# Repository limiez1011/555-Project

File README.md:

# blinky
Little led board that uses a 555 timer to clock a decade counter.

## Functionality
The NE555 is in AStable mode which creates a PWM signal that feeds into the CD4017, the PWM output is adjustable through the potentiometer, the CD4017 has 10 output pins which turn on sequentially every time it recieves a clock pulse, on our PCB this means that the leds will turn on after another in a circular pattern.

## BOM
- 1x NE555 Timer
- 1x CD4017 Decade counter
- 1x Potentiometer
- 2x Capacitors
- 2x Resistors
- 10x LED's

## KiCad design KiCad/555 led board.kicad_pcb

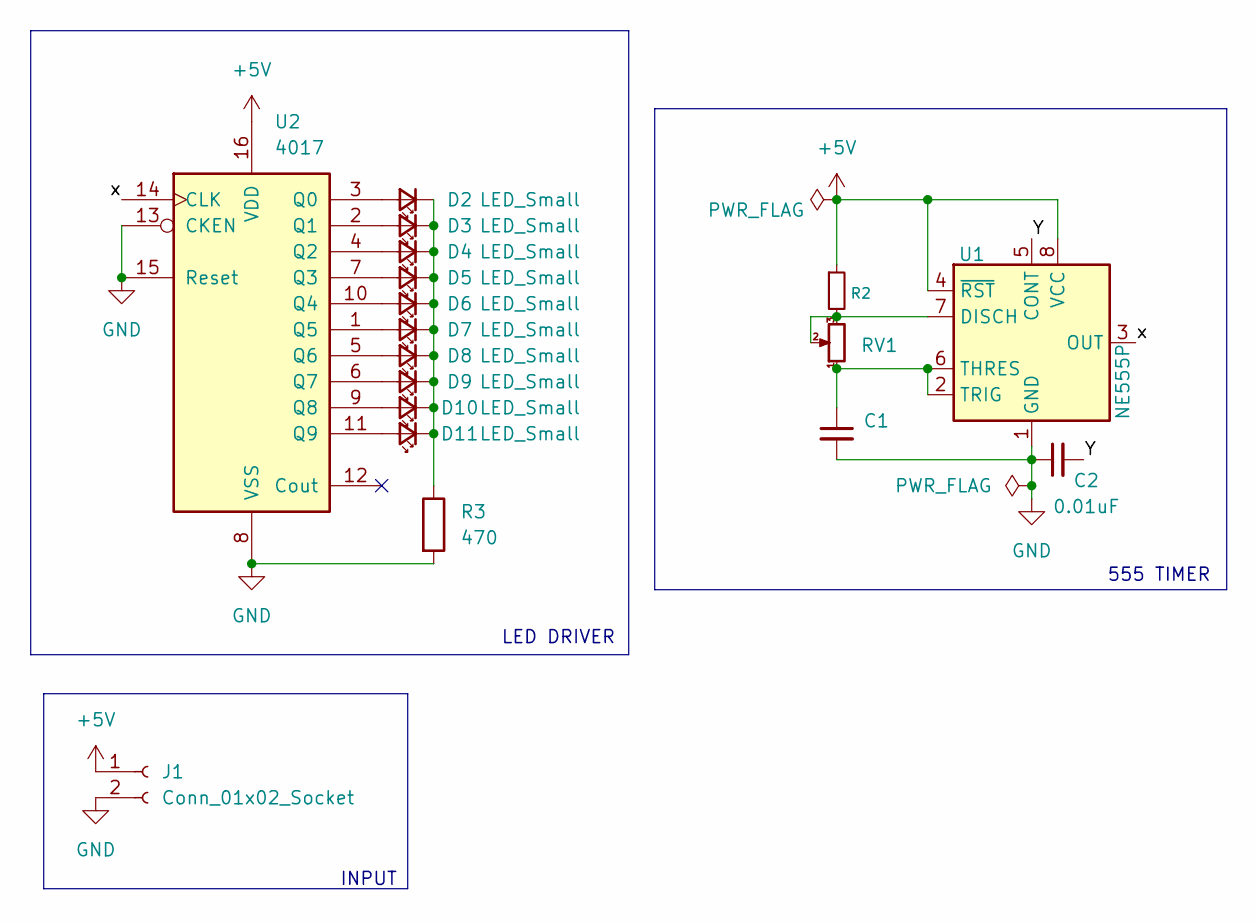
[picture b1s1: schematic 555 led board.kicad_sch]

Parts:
C1: C_Small; CP_Radial_D5.0mm_P2.00mm
C2: 0.01uF; C_Disc_D7.5mm_W2.5mm_P5.00mm
D2, D3, D4, D5, D6, D7, D8, D9, D10, D11: LED_Small; LED_D3.0mm
J1: Conn_01x02_Socket; PinHeader_1x02_P2.54mm_Vertical
R2: R_Small; R_Axial_DIN0207_L6.3mm_D2.5mm_P7.62mm_Horizontal
R3: 470; R_Axial_DIN0207_L6.3mm_D2.5mm_P7.62mm_Horizontal
RV1: R_Potentiometer_Small; Potentiometer_Vishay_T93YA_Vertical
U1: NE555P; DIP-8_W7.62mm
U2: 4017; DIP794W45P254L1969H508Q16

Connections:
+5V: J1.1, R2.1, U1.4 (~RST), U1.8 (VCC), U2.16 (VDD)
/Y: C2.2, U1.5 (CONT)
/x: U1.3 (OUT), U2.14 (CLK)
GND: C1.2, C2.1, J1.2, R3.2, U1.1 (GND), U2.8 (VSS), U2.13 (CKEN), U2.15 (Reset)
unnamed: D2.2 (A), U2.3 (Q0)
unnamed: D3.2 (A), U2.2 (Q1)
unnamed: D4.2 (A), U2.4 (Q2)
unnamed: D5.2 (A), U2.7 (Q3)
unnamed: D6.2 (A), U2.10 (Q4)
unnamed: D7.2 (A), U2.1 (Q5)
unnamed: D8.2 (A), U2.5 (Q6)
unnamed: D9.2 (A), U2.6 (Q7)
unnamed: D10.2 (A), U2.9 (Q8)
unnamed: D2.1 (K), D3.1 (K), D4.1 (K), D5.1 (K), D6.1 (K), D7.1 (K), D8.1 (K), D9.1 (K), D10.1 (K), D11.1 (K), R3.1
unnamed: D11.2 (A), U2.11 (Q9)
unnamed: R2.2, RV1.2, RV1.3, U1.7 (DISCH)
unnamed: C1.1, RV1.1, U1.2 (TRIG), U1.6 (THRES)

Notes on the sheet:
INPUT
LED DRIVER
555 TIMER

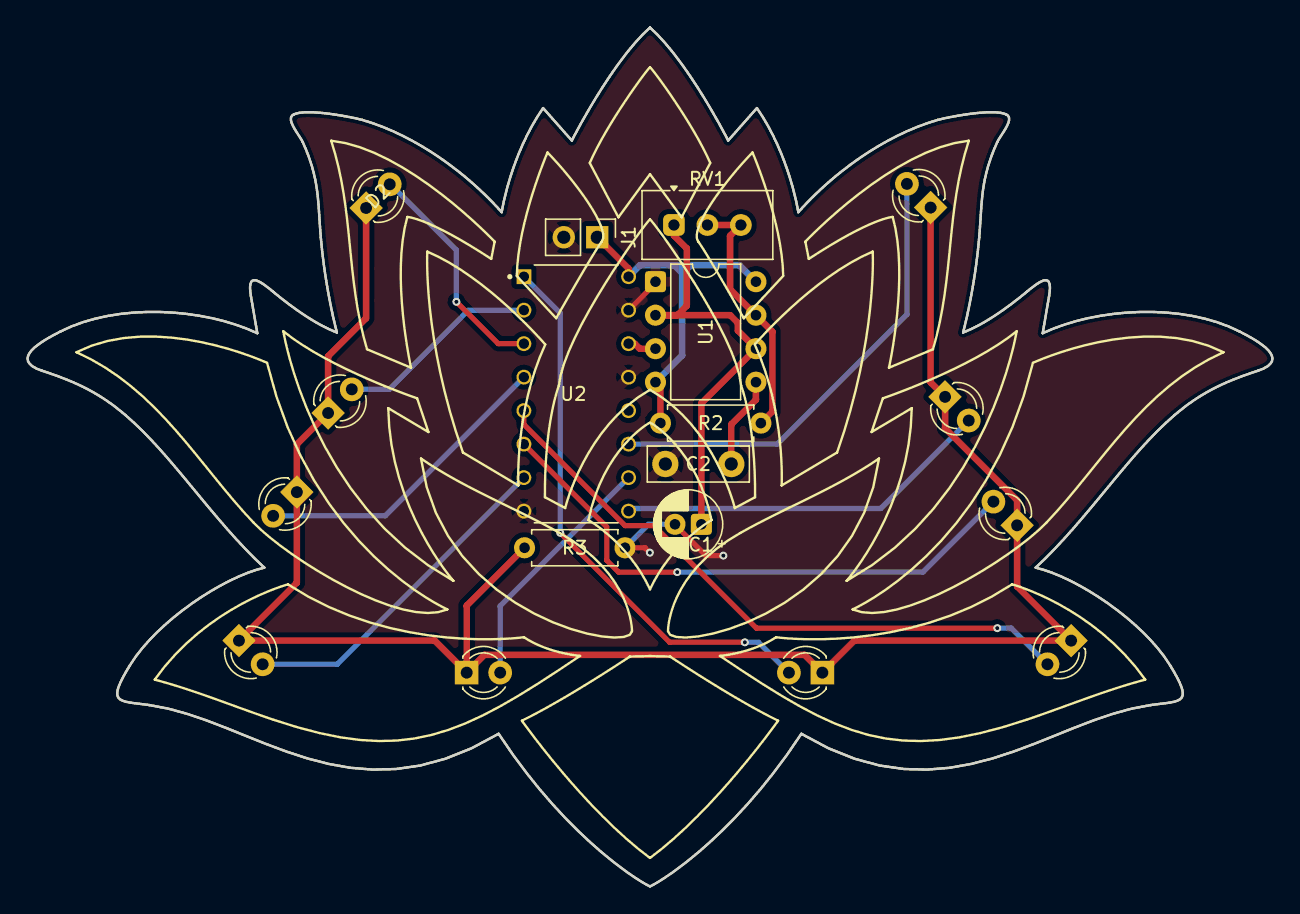
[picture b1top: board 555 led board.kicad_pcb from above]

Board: 2 copper layers, 94.4 x 65.1 mm, 18 parts (0 on the bottom side), 17 nets.

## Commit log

2026-04-28 Enhance README with timer details and image
    Added a description of the 555 timer and included an image.
2026-04-28 Create e
2026-05-03 Enhance README with functionality and BOM details
    Added functionality and BOM sections to README.
2026-05-22 Create x
